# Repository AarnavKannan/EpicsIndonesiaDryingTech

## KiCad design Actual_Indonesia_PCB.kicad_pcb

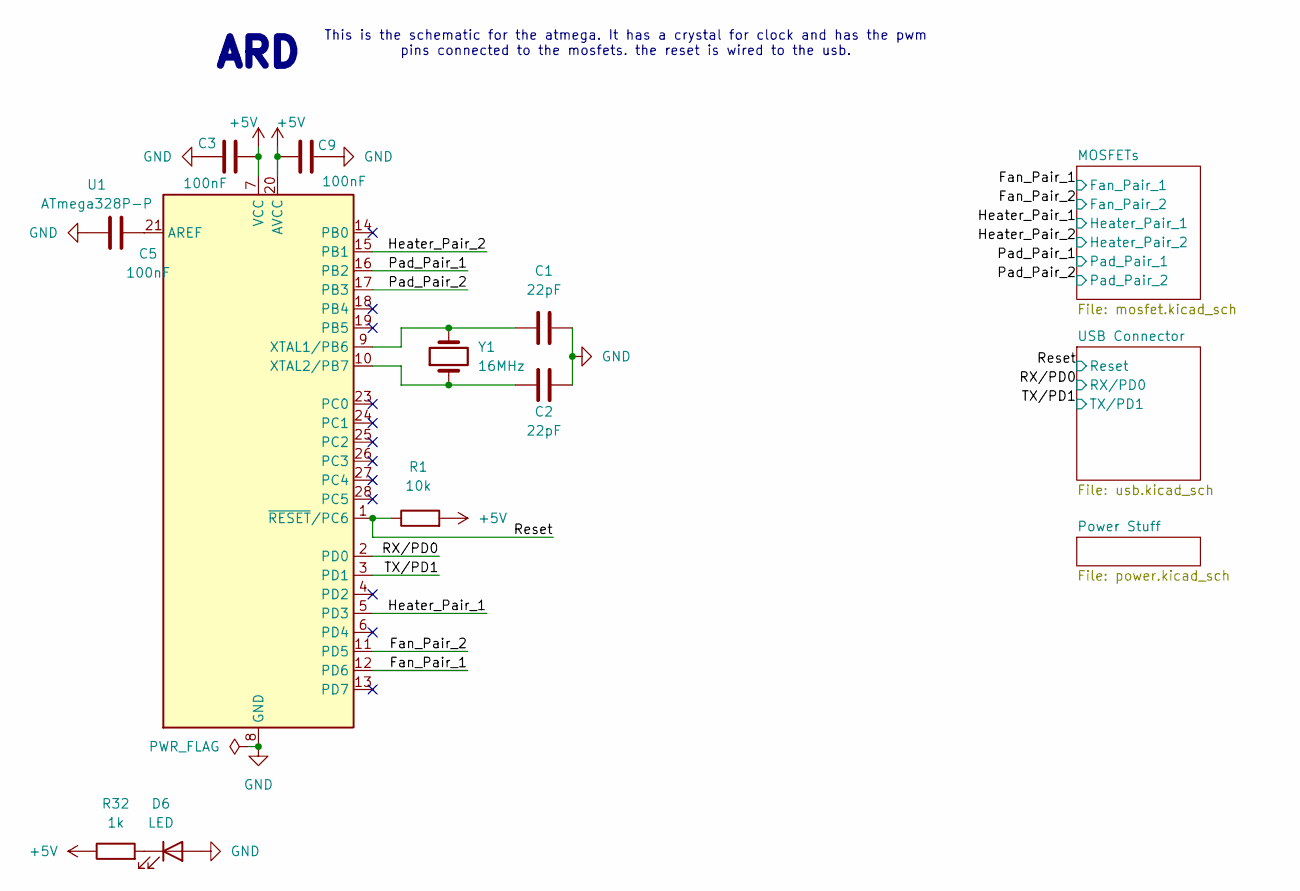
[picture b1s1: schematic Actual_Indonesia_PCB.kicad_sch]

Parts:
C1, C2: 22pF; C_0805_2012Metric
C3, C5, C9: 100nF; C_0805_2012Metric
D6: LED; LED_0805_2012Metric
R1: 10k; R_0805_2012Metric
R32: 1k; R_0805_2012Metric
U1: ATmega328P-P; DIP-28_W7.62mm
Y1: 16MHz; Crystal_HC49-U_Vertical

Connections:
+5V: C3.2, C9.2, R1.2, R32.1, U1.7 (VCC), U1.20 (AVCC); also elsewhere on the board
/Fan_Pair_1: U1.12 (PD6); also elsewhere on the board
/Fan_Pair_2: U1.11 (PD5); also elsewhere on the board
/Heater_Pair_1: U1.5 (PD3); also elsewhere on the board
/Heater_Pair_2: U1.15 (PB1); also elsewhere on the board
/Pad_Pair_1: U1.16 (PB2); also elsewhere on the board
/Pad_Pair_2: U1.17 (PB3); also elsewhere on the board
/RX/PD0: U1.2 (PD0); also elsewhere on the board
/Reset: R1.1, U1.1 (~RESET/PC6); also elsewhere on the board
/TX/PD1: U1.3 (PD1); also elsewhere on the board
GND: C1.2, C2.2, C3.1, C5.1, C9.1, D6.2 (A), U1.8 (GND), U1.22 (GND); also elsewhere on the board
unnamed: D6.1 (K), R32.2
unnamed: C5.2, U1.21 (AREF)
unnamed: C1.1, U1.9 (XTAL1/PB6), Y1.2
unnamed: C2.1, U1.10 (XTAL2/PB7), Y1.1

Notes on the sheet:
ARD
This is the schematic for the atmega. It has a crystal for clock and has the pwm pins connected to the mosfets. the reset is wired to the usb.

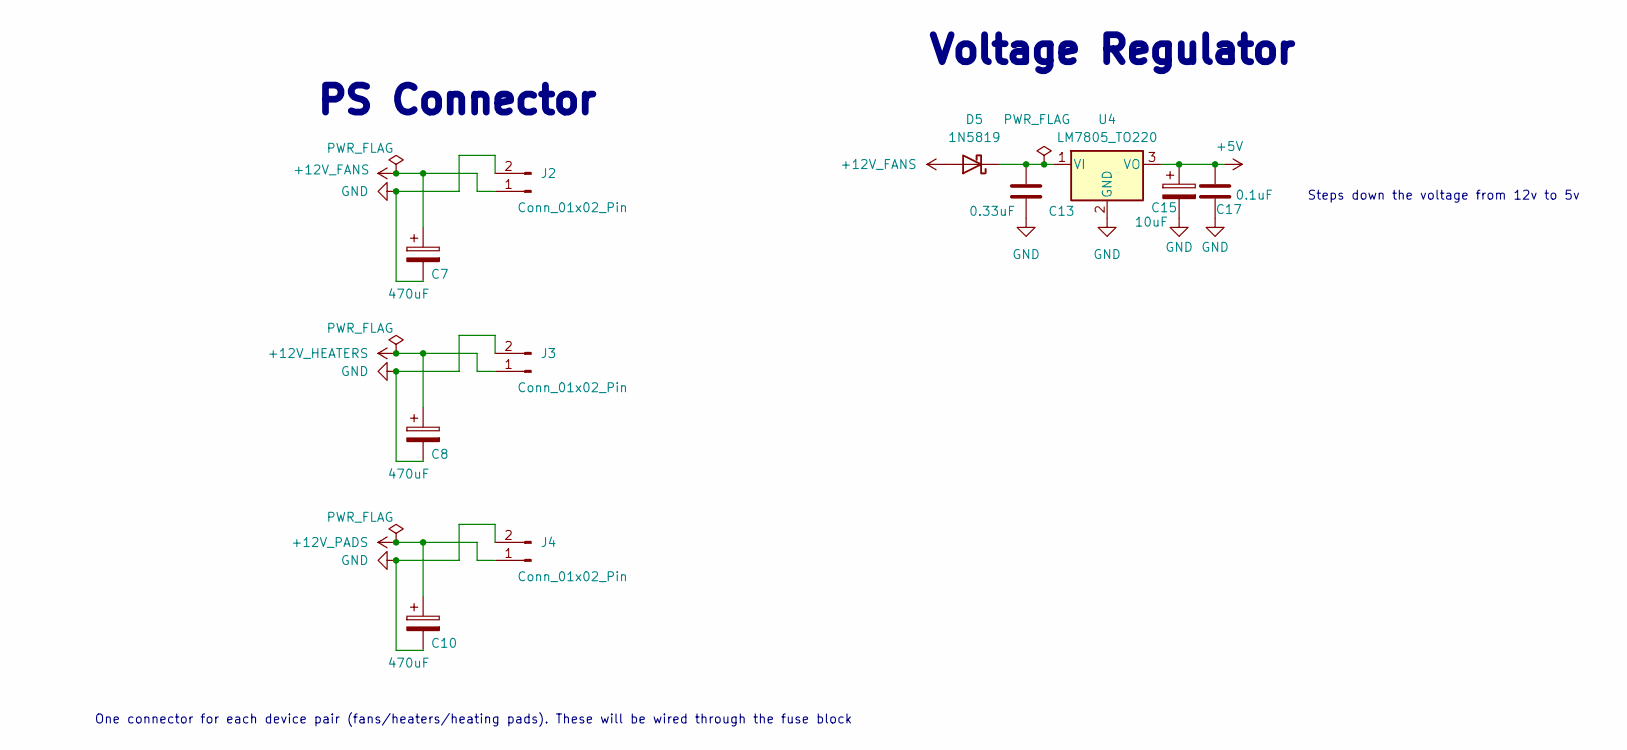
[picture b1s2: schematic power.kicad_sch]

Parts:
C7, C8, C10: 470uF; CP_Radial_D10.0mm_P5.00mm
C13: 0.33uF; C_0805_2012Metric
C15: 10uF; CP_Radial_D5.0mm_P2.00mm
C17: 0.1uF; C_0805_2012Metric
D5: 1N5819; D_DO-41_SOD81_P10.16mm_Horizontal
J2, J3, J4: Conn_01x02_Pin; AMASS_XT60-M_1x02_P7.20mm_Vertical
U4: LM7805_TO220; TO-220-3_Vertical

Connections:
+5V: C15.1, C17.1, U4.3 (VO); also elsewhere on the board
+12V_FANS: C7.1, D5.2 (A), J2.1; also elsewhere on the board
+12V_HEATERS: C8.1, J3.1; also elsewhere on the board
+12V_PADS: C10.1, J4.1; also elsewhere on the board
GND: C7.2, C8.2, C10.2, C13.1, C15.2, C17.2, J2.2, J3.2, J4.2, U4.2 (GND); also elsewhere on the board
unnamed: C13.2, D5.1 (K), U4.1 (VI)

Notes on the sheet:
PS Connector
Voltage Regulator
One connector for each device pair (fans/heaters/heating pads). These will be wired through the fuse block
Steps down the voltage from 12v to 5v

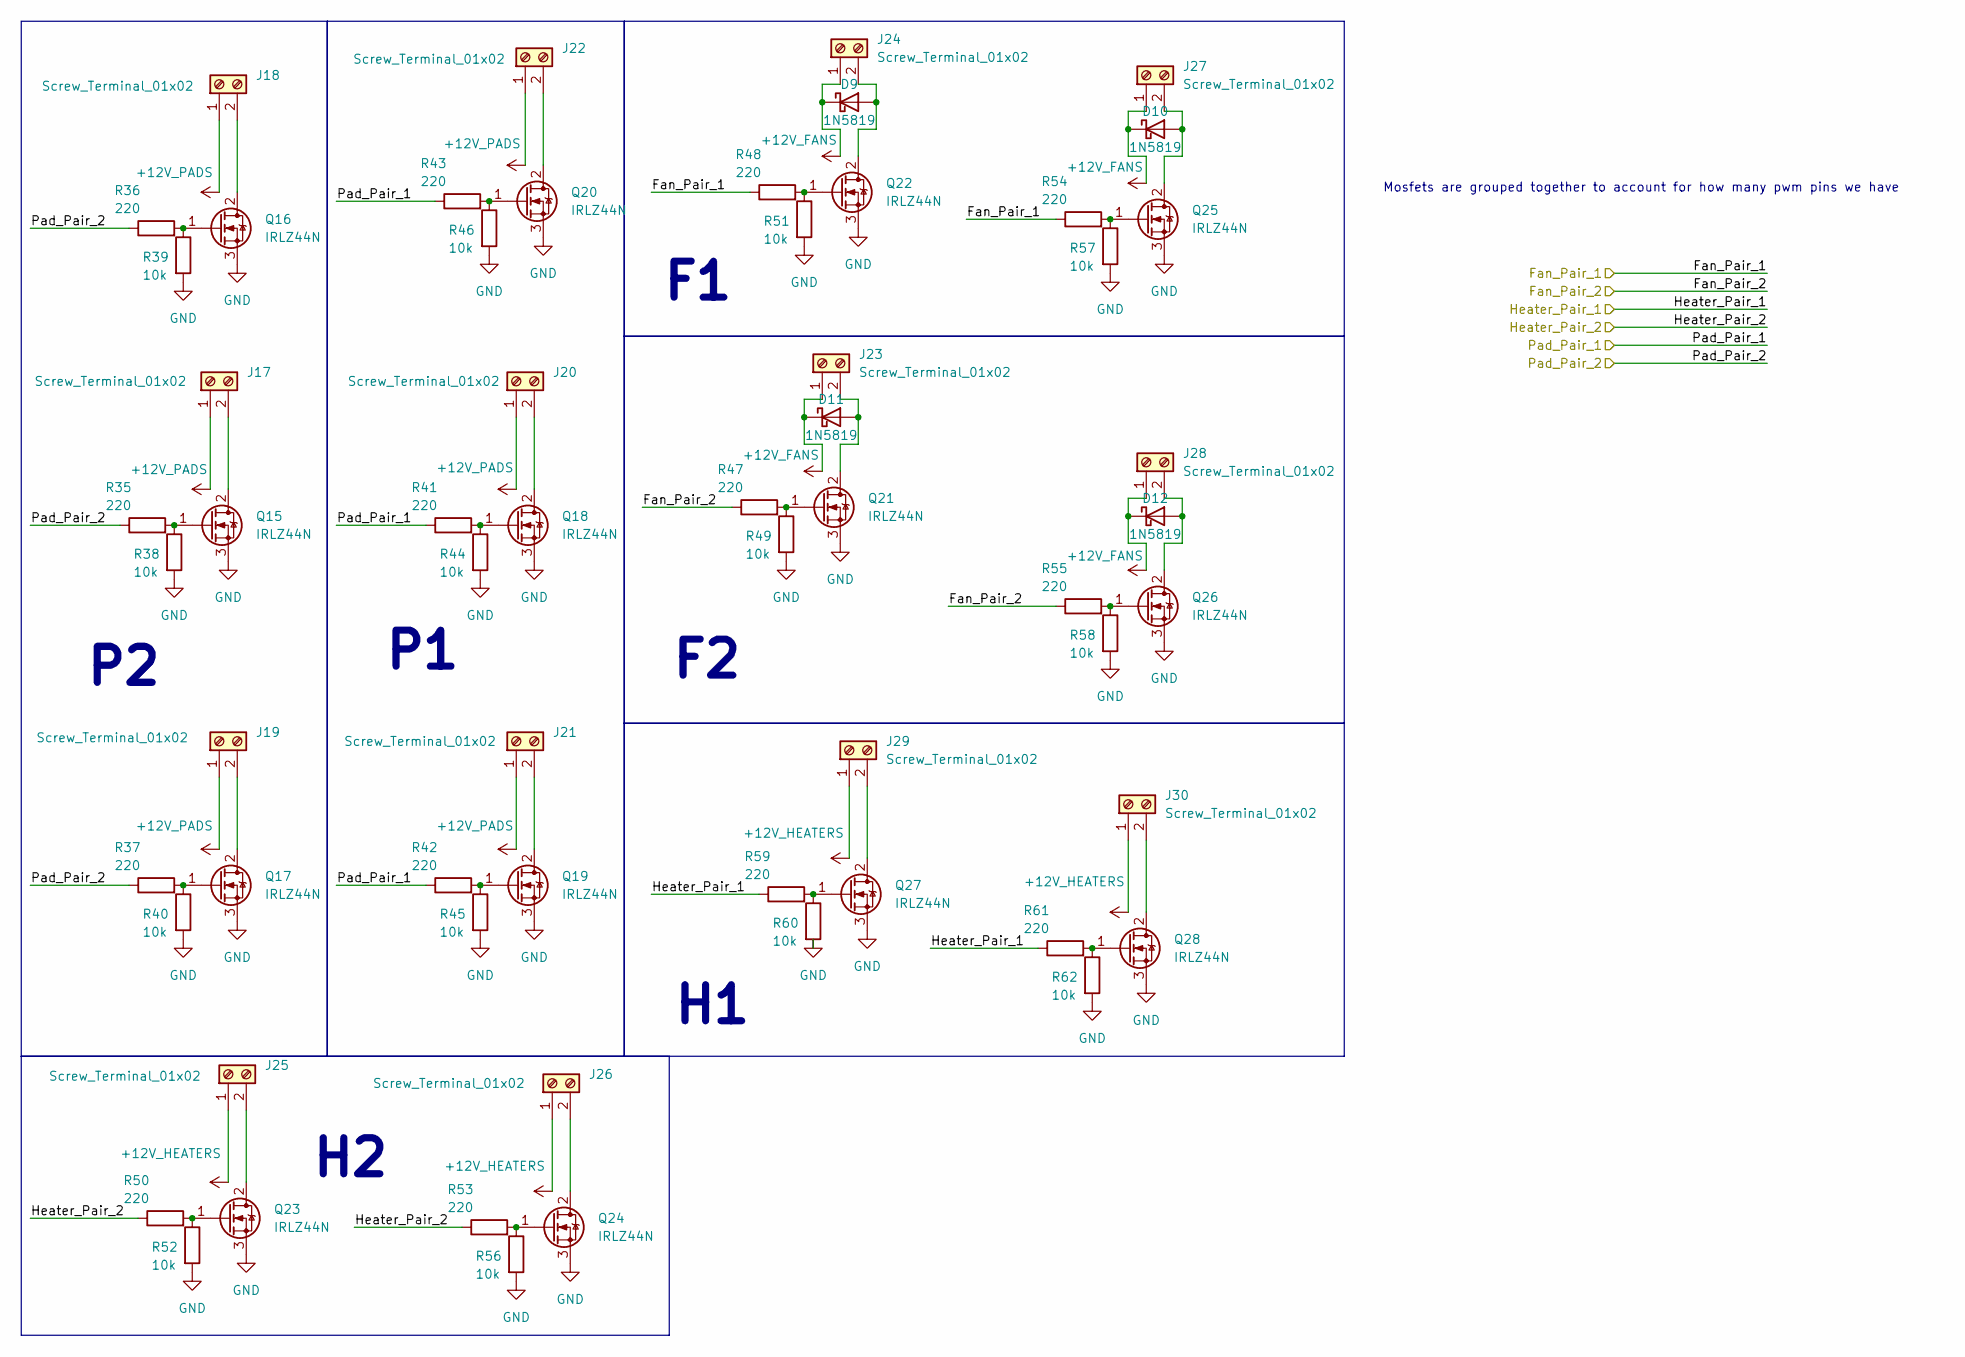
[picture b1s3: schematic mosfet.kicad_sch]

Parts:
D9, D10, D11, D12: 1N5819; D_DO-41_SOD81_P10.16mm_Horizontal
J17, J18, J19, J20, J21, J22, J23, J24, J25, J26, J27, J28, J29, J30: Screw_Terminal_01x02; TerminalBlock_Phoenix_MKDS-1,5-2_1x02_P5.00mm_Horizontal
Q15, Q16, Q17, Q18, Q19, Q20, Q21, Q22, Q23, Q24, Q25, Q26, Q27, Q28: IRLZ44N; TO-220-3_Vertical
R35, R36, R37, R41, R42, R43, R47, R48, R50, R53, R54, R55, R59, R61: 220; R_0805_2012Metric
R38, R39, R40, R44, R45, R46, R49, R51, R52, R56, R57, R58, R60, R62: 10k; R_0805_2012Metric

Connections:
+12V_FANS: D9.1 (K), D10.1 (K), D11.1 (K), D12.1 (K), J23.1, J24.1, J27.1, J28.1; also elsewhere on the board
+12V_HEATERS: J25.1, J26.1, J29.1, J30.1; also elsewhere on the board
+12V_PADS: J17.1, J18.1, J19.1, J20.1, J21.1, J22.1; also elsewhere on the board
/Fan_Pair_1: R48.1, R54.1; also elsewhere on the board
/Fan_Pair_2: R47.1, R55.1; also elsewhere on the board
/Heater_Pair_1: R59.1, R61.1; also elsewhere on the board
/Heater_Pair_2: R50.1, R53.1; also elsewhere on the board
/Pad_Pair_1: R41.1, R42.1, R43.1; also elsewhere on the board
/Pad_Pair_2: R35.1, R36.1, R37.1; also elsewhere on the board
GND: Q15.3 (S), Q16.3 (S), Q17.3 (S), Q18.3 (S), Q19.3 (S), Q20.3 (S), Q21.3 (S), Q22.3 (S), Q23.3 (S), Q24.3 (S), Q25.3 (S), Q26.3 (S), Q27.3 (S), Q28.3 (S), R38.2, R39.2, R40.2, R44.2, R45.2, R46.2, R49.2, R51.2, R52.2, R56.2, R57.2, R58.2, R60.2, R62.2; also elsewhere on the board
unnamed: D9.2 (A), J24.2, Q22.2 (D)
unnamed: D10.2 (A), J27.2, Q25.2 (D)
unnamed: D11.2 (A), J23.2, Q21.2 (D)
unnamed: D12.2 (A), J28.2, Q26.2 (D)
unnamed: J17.2, Q15.2 (D)
unnamed: J18.2, Q16.2 (D)
unnamed: J19.2, Q17.2 (D)
unnamed: J20.2, Q18.2 (D)
unnamed: J21.2, Q19.2 (D)
unnamed: J22.2, Q20.2 (D)
unnamed: J25.2, Q23.2 (D)
unnamed: J26.2, Q24.2 (D)
unnamed: J29.2, Q27.2 (D)
unnamed: J30.2, Q28.2 (D)
unnamed: Q15.1 (G), R35.2, R38.1
unnamed: Q16.1 (G), R36.2, R39.1
unnamed: Q17.1 (G), R37.2, R40.1
unnamed: Q18.1 (G), R41.2, R44.1
unnamed: Q19.1 (G), R42.2, R45.1
unnamed: Q20.1 (G), R43.2, R46.1
unnamed: Q21.1 (G), R47.2, R49.1
unnamed: Q22.1 (G), R48.2, R51.1
unnamed: Q23.1 (G), R50.2, R52.1
unnamed: Q24.1 (G), R53.2, R56.1
unnamed: Q25.1 (G), R54.2, R57.1
unnamed: Q26.1 (G), R55.2, R58.1
unnamed: Q27.1 (G), R59.2, R60.1
unnamed: Q28.1 (G), R61.2, R62.1

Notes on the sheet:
Mosfets are grouped together to account for how many pwm pins we have

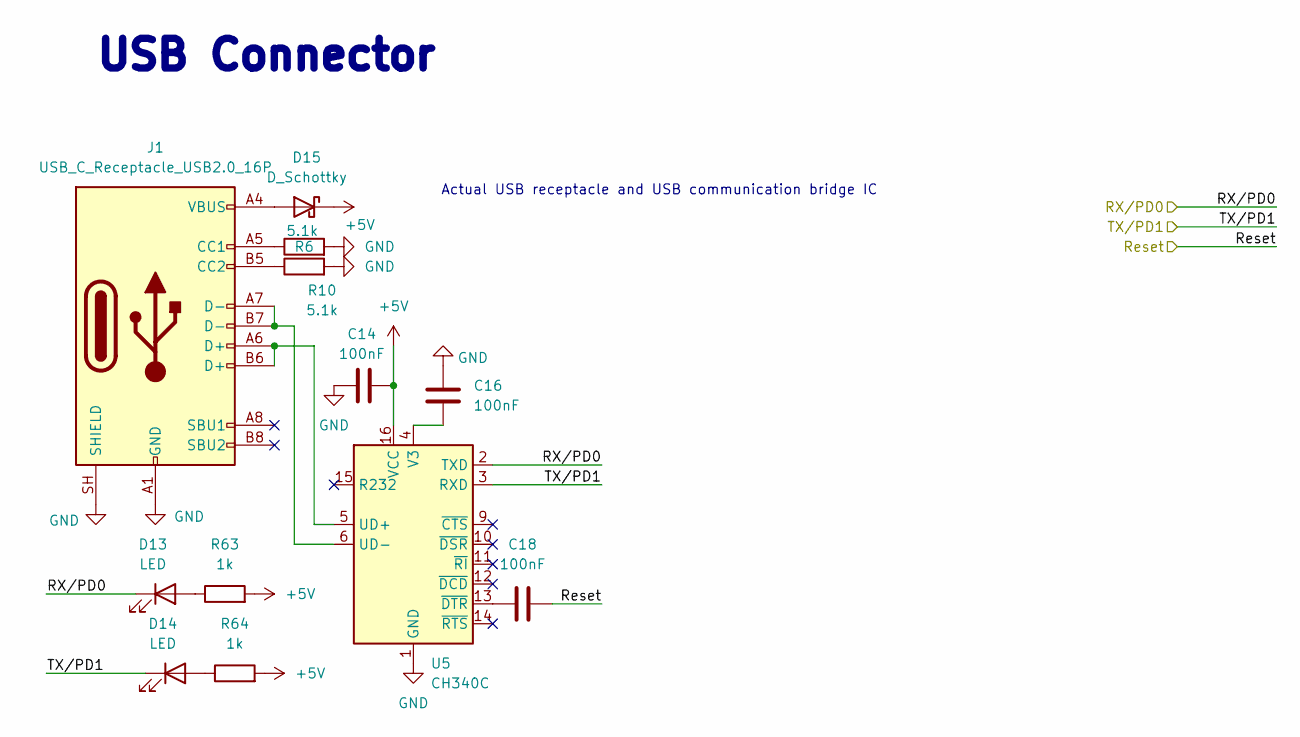
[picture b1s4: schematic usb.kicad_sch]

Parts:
C14, C16, C18: 100nF; C_0805_2012Metric
D13, D14: LED; LED_0805_2012Metric
D15: D_Schottky; D_DO-41_SOD81_P10.16mm_Horizontal
J1: USB_C_Receptacle_USB2.0_16P; USB_C_Receptacle_HRO_TYPE-C-31-M-12
R6, R10: 5.1k; R_0805_2012Metric
R63, R64: 1k; R_0805_2012Metric
U5: CH340C; SOIC-16_3.9x9.9mm_P1.27mm

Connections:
+5V: C14.2, D15.1 (K), R63.2, R64.2, U5.16 (VCC); also elsewhere on the board
/RX/PD0: D13.1 (K), U5.2 (TXD); also elsewhere on the board
/Reset: C18.2; also elsewhere on the board
/TX/PD1: D14.1 (K), U5.3 (RXD); also elsewhere on the board
GND: C14.1, C16.1, J1.A1 (GND), J1.A12 (GND), J1.B1 (GND), J1.B12 (GND), J1.SH (SHIELD), R6.2, R10.2, U5.1 (GND); also elsewhere on the board
unnamed: D13.2 (A), R63.1
unnamed: D14.2 (A), R64.1
unnamed: D15.2 (A), J1.A4 (VBUS), J1.A9 (VBUS), J1.B4 (VBUS), J1.B9 (VBUS)
unnamed: J1.A5 (CC1), R6.1
unnamed: J1.B5 (CC2), R10.1
unnamed: J1.A6 (D+), J1.B6 (D+), U5.5 (UD+)
unnamed: J1.A7 (D-), J1.B7 (D-), U5.6 (UD-)
unnamed: C16.2, U5.4 (V3)
unnamed: C18.1, U5.13 (~DTR)

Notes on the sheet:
USB Connector
Actual USB receptacle and USB communication bridge IC

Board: 2 copper layers, 93 parts (0 on the bottom side), 56 nets, no tracks yet.
